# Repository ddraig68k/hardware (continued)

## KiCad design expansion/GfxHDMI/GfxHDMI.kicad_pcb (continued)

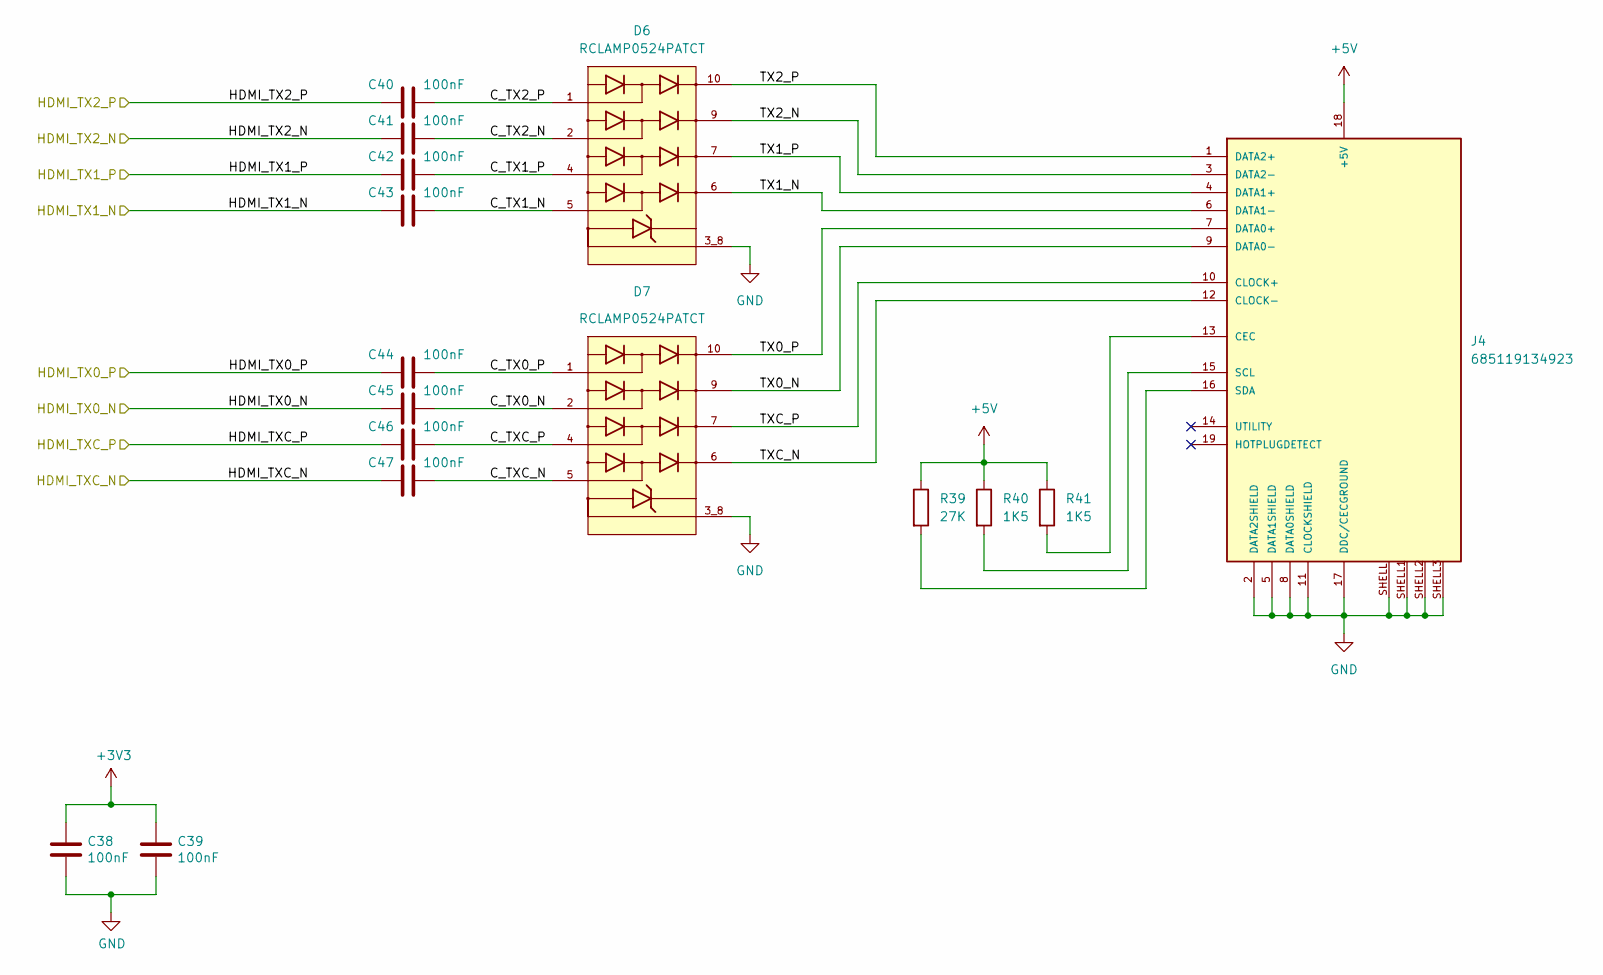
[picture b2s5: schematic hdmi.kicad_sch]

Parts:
C38, C39: 100nF; C_0805_2012Metric
C40, C41, C42, C43, C44, C45, C46, C47: 100nF; C_0603_1608Metric
D6, D7: RCLAMP0524PATCT; DIO_RCLAMP0524PATCT
J4: 685119134923
R39: 27K; R_0805_2012Metric
R40, R41: 1K5; R_0805_2012Metric

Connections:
+3V3: C38.1, C39.1; also elsewhere on the board
+5V: J4.18 (+5V), R39.1, R40.1, R41.1; also elsewhere on the board
/HDMI/C_TX0_N: C45.2, D7.2
/HDMI/C_TX0_P: C44.2, D7.1
/HDMI/C_TX1_N: C43.2, D6.5
/HDMI/C_TX1_P: C42.2, D6.4
/HDMI/C_TX2_N: C41.2, D6.2
/HDMI/C_TX2_P: C40.2, D6.1
/HDMI/C_TXC_N: C47.2, D7.5
/HDMI/C_TXC_P: C46.2, D7.4
/HDMI/HDMI_TX0_N: C45.1; also elsewhere on the board
/HDMI/HDMI_TX0_P: C44.1; also elsewhere on the board
/HDMI/HDMI_TX1_N: C43.1; also elsewhere on the board
/HDMI/HDMI_TX1_P: C42.1; also elsewhere on the board
/HDMI/HDMI_TX2_N: C41.1; also elsewhere on the board
/HDMI/HDMI_TX2_P: C40.1; also elsewhere on the board
/HDMI/HDMI_TXC_N: C47.1; also elsewhere on the board
/HDMI/HDMI_TXC_P: C46.1; also elsewhere on the board
/HDMI/TX0_N: D7.9, J4.9 (DATA0-)
/HDMI/TX0_P: D7.10, J4.7 (DATA0+)
/HDMI/TX1_N: D6.6, J4.6 (DATA1-)
/HDMI/TX1_P: D6.7, J4.4 (DATA1+)
/HDMI/TX2_N: D6.9, J4.3 (DATA2-)
/HDMI/TX2_P: D6.10, J4.1 (DATA2+)
/HDMI/TXC_N: D7.6, J4.12 (CLOCK-)
/HDMI/TXC_P: D7.7, J4.10 (CLOCK+)
GND: C38.2, C39.2, D6.3_8, D7.3_8, J4.2 (DATA2SHIELD), J4.5 (DATA1SHIELD), J4.8 (DATA0SHIELD), J4.11 (CLOCKSHIELD), J4.17 (DDC/CECGROUND), J4.SHELL, J4.SHELL1, J4.SHELL2, J4.SHELL3; also elsewhere on the board
unnamed: J4.13 (CEC), R41.2
unnamed: J4.15 (SCL), R40.2
unnamed: J4.16 (SDA), R39.2

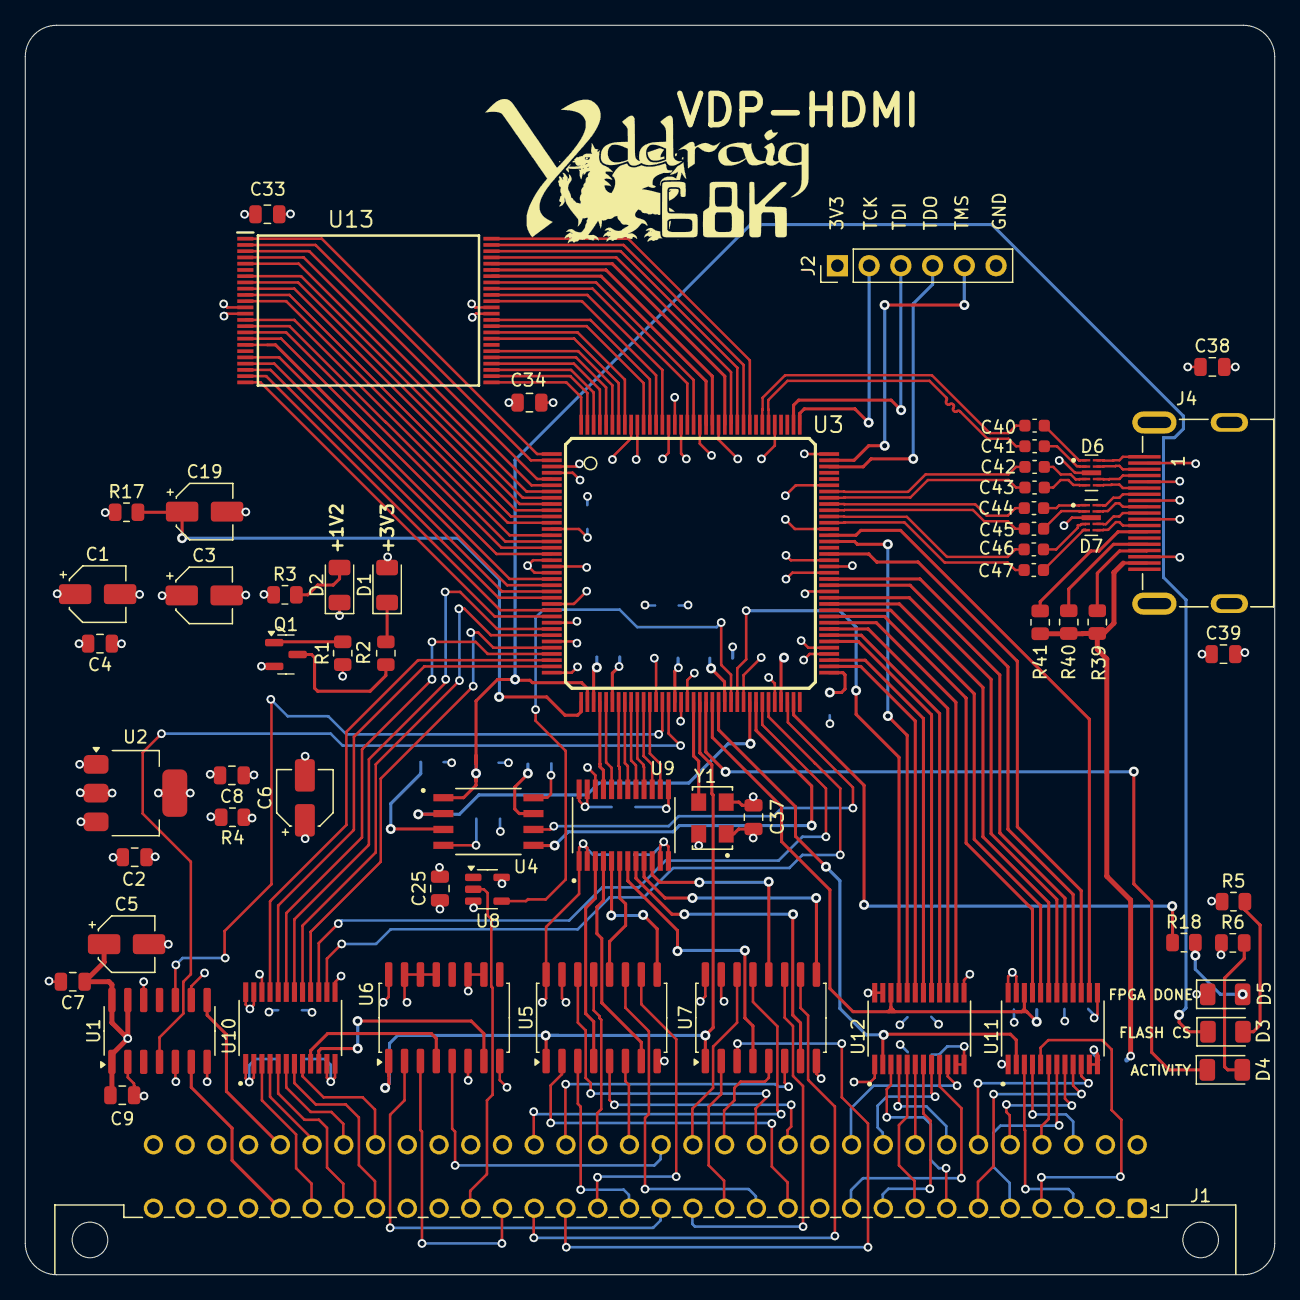
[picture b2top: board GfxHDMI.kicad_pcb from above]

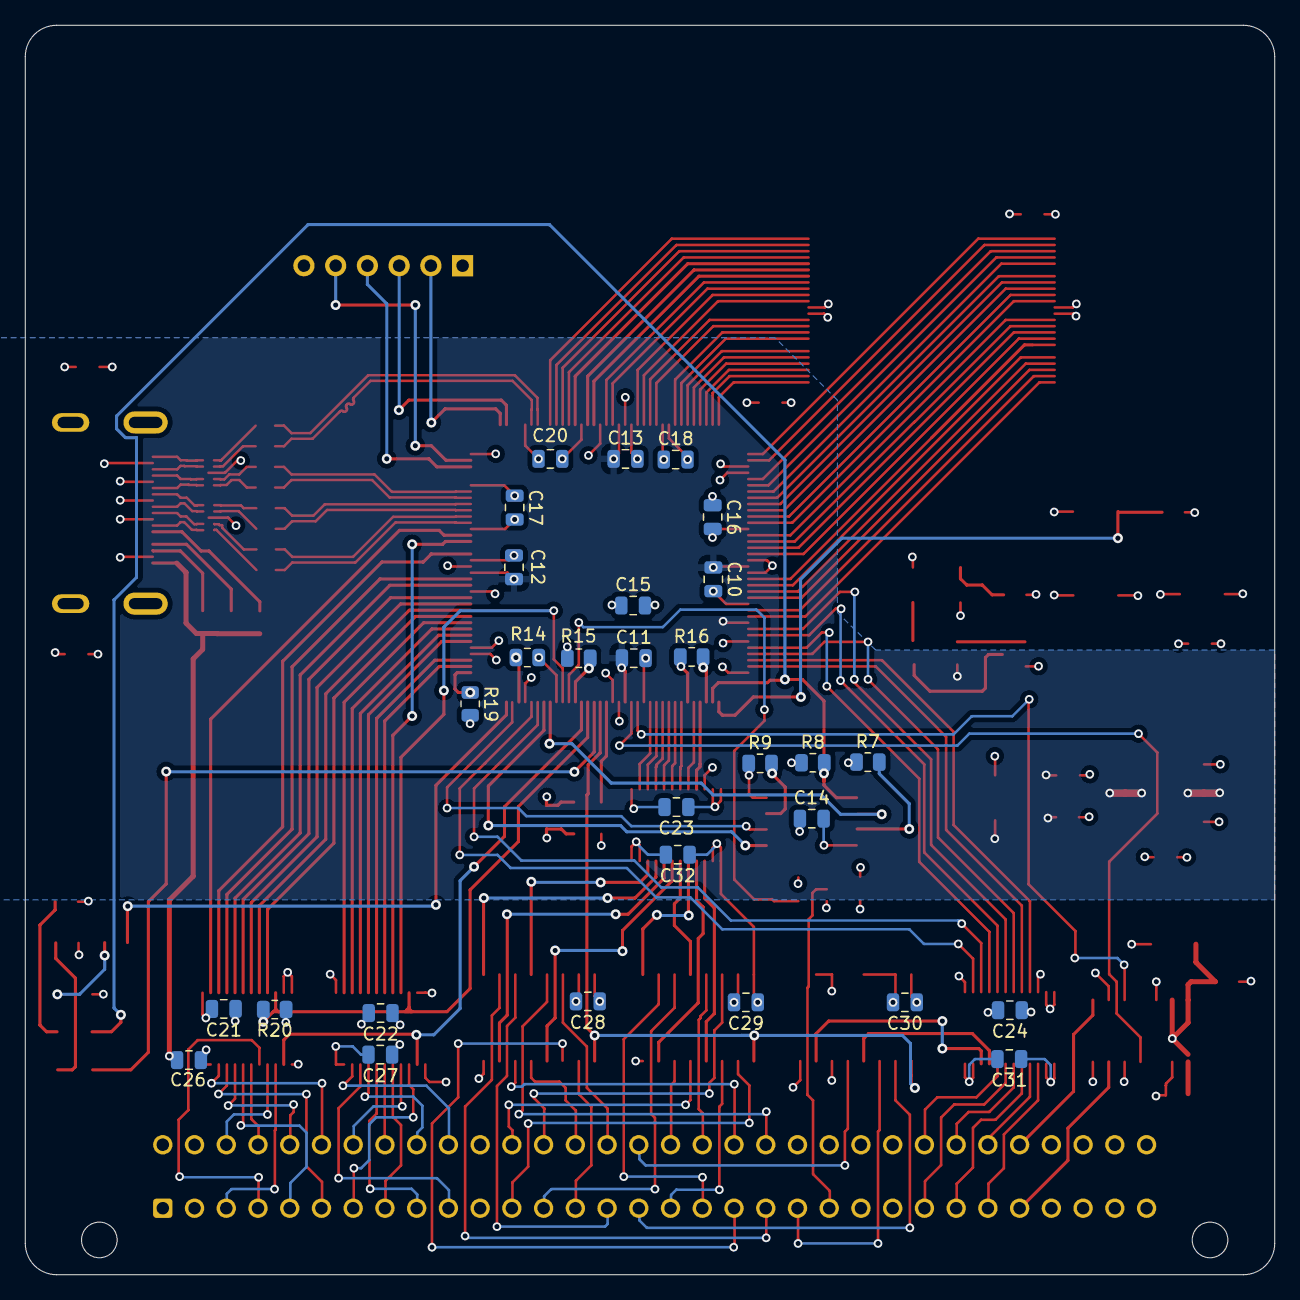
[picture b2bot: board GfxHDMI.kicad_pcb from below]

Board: 4 copper layers, 100.0 x 100.0 mm, 90 parts (29 on the bottom side), 189 nets.

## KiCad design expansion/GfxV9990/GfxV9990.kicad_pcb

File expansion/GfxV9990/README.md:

# V9990 Video card

The V9990 was intended as a successor to the V9958 (or supposedly a stripped down version of the never finished Yamaha V9978), but while the other chips in the range had backwards compatibility with the previous generation, the V9990 has some similar functionality but lacks the backwards compatibility.

Still, the V9990 has impressive specifications for the time, some of the features include:

Game Specifications:

For this type, there are two pattern display modes.
* P1 (Display resolution 256 x 212 2 screens)
* P2 (Display resolution 512 x 212)

*Various highly advanced functions are available such as powerful sprite function and omnidirectional scroll function.*

AV Specifications:

For this type, there are four kinds of bitmap display modes which can be displayed on the NTSC or PAL frequency monitor as follows.
* B1 (Display resolution 256 x 212)
* B2 (Display resolution 384 x 240)
* B3 (Display resolution 512 x 212)
* B4 (Display resolution 768 x 240)

*Capable of doubling the resolution in the vertical direction by using interlace.*
*Display is possible up to 32,768 colors/dot.*
*Built-in color palette (64 colors selected out of 32,768 colors).*
*Omnidirectional smooth scrolling is possible.*

Like the [V9958](/expansion/GfxV9958) card, the V9990 has Composite, S-Video and RGB output. The board has 518K of RAM installed and again uses CXA2075M encoder to provide the video output signals. 

**V9990 Text mode**

**Rygar scrolling test:** https://www.youtube.com/watch?v=J7Ad2eaiAFY

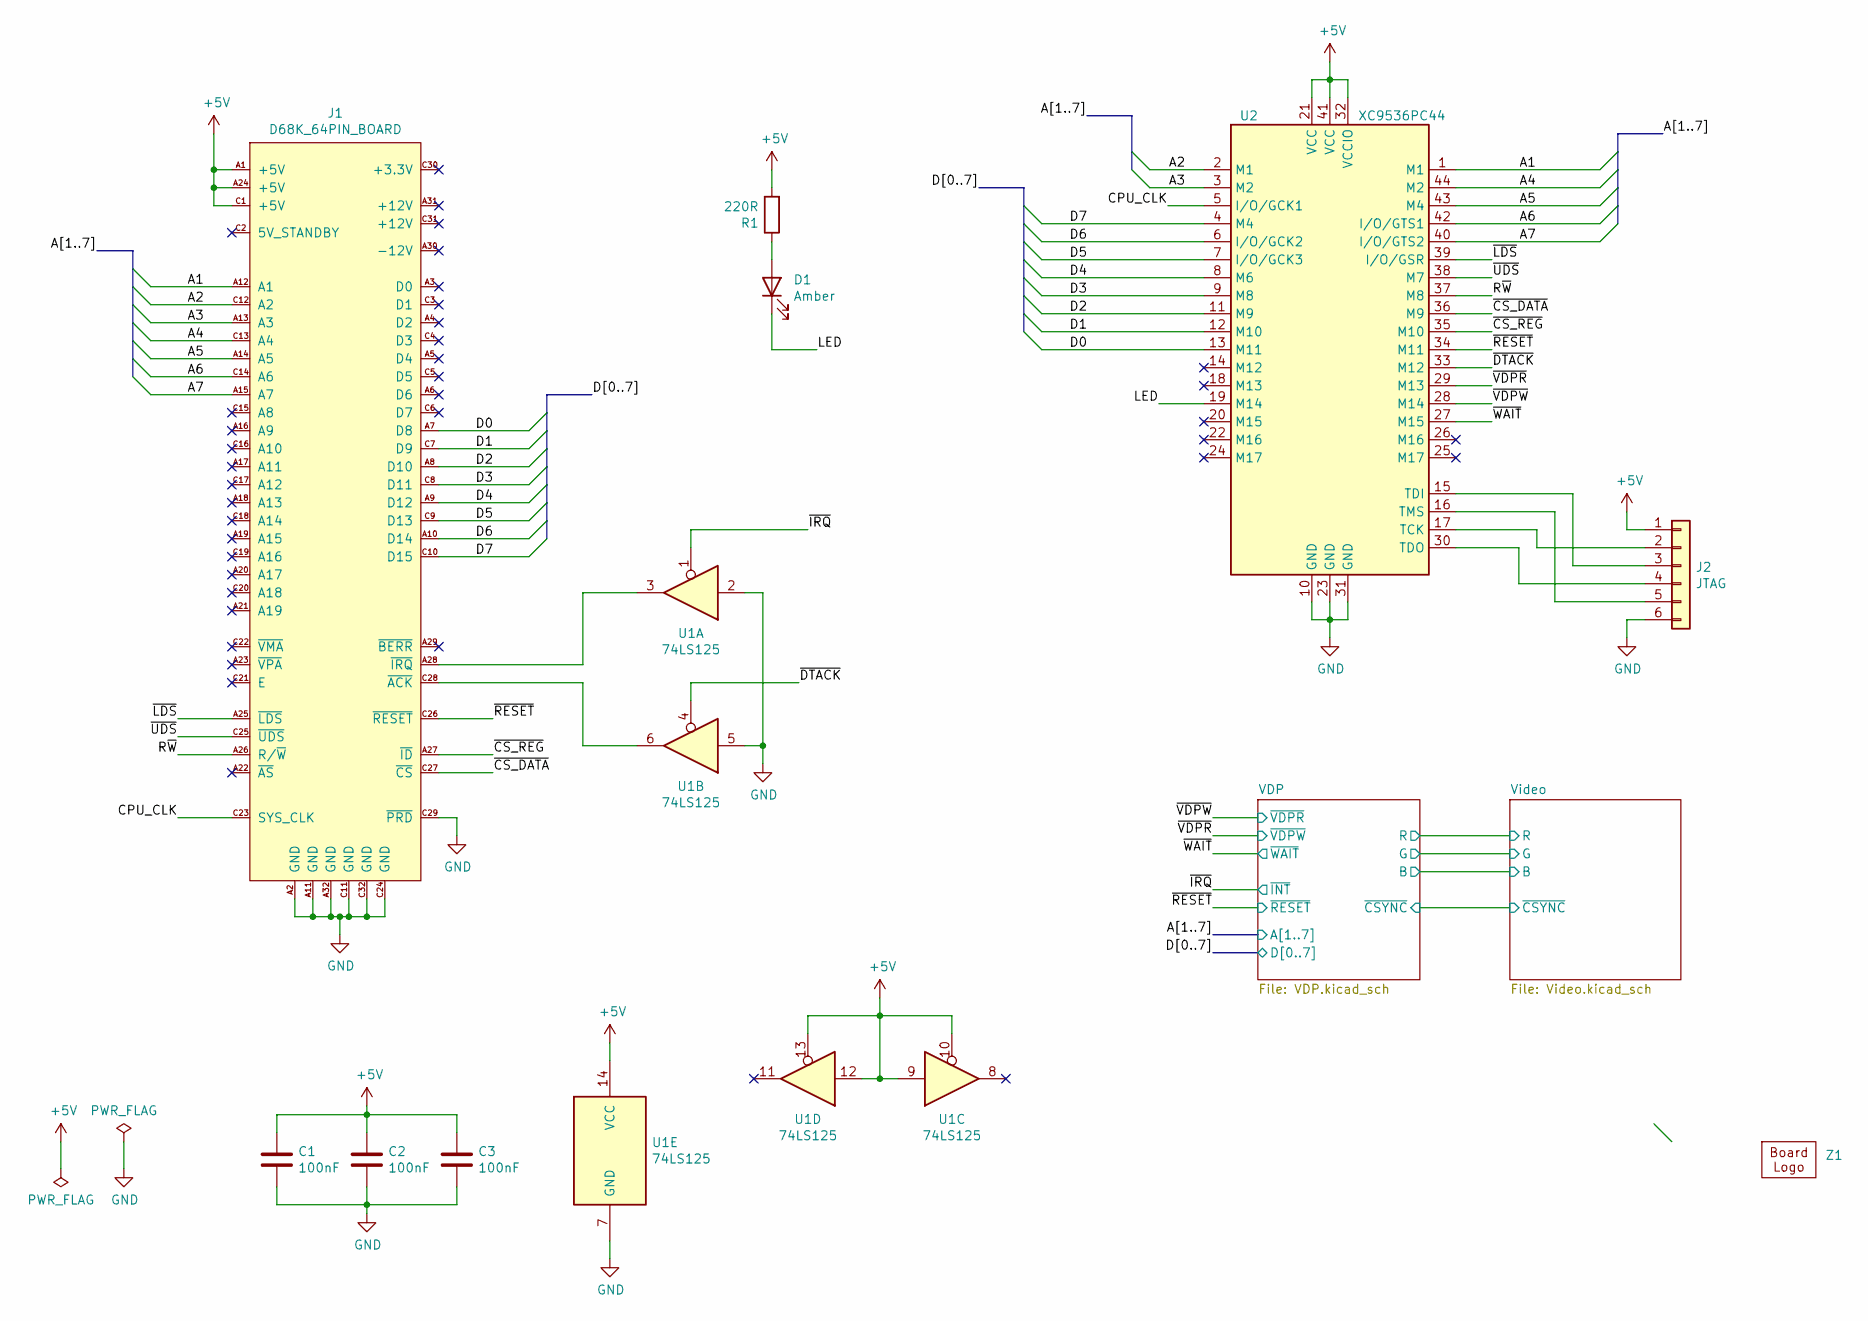
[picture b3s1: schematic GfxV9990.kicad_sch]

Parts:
C1, C2, C3: 100nF; C_0805_2012Metric
D1: Amber; LED_1206_3216Metric
J1: D68K_64PIN_BOARD; DIN41612_C_2x32_Male_Horizontal_THT
J2: JTAG; PinHeader_1x06_P2.54mm_Vertical
R1: 220R; LED_0805_2012Metric
U1: 74LS125; SO-14_3.9x8.65mm_P1.27mm
U2: XC9536PC44; PLCC-44_THT-Socket
Z1: Ddraig68k-26mm

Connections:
+5V: C1.1, C2.1, C3.1, J1.A1 (+5V), J1.A24 (+5V), J1.C1 (+5V), J2.1, R1.2, U1.9, U1.10, U1.12, U1.13, U1.14 (VCC), U2.21 (VCC), U2.32 (VCCIO), U2.41 (VCC); also elsewhere on the board
/A1: J1.A12 (A1), U2.1 (M1); also elsewhere on the board
/A2: J1.C12 (A2), U2.2 (M1); also elsewhere on the board
/A3: J1.A13 (A3), U2.3 (M2); also elsewhere on the board
/A4: J1.C13 (A4), U2.44 (M2); also elsewhere on the board
/A5: J1.A14 (A5), U2.43 (M4)
/A6: J1.C14 (A6), U2.42 (I/O/GTS1)
/A7: J1.A15 (A7), U2.40 (I/O/GTS2)
/CPU_CLK: J1.C23 (SYS_CLK), U2.5 (I/O/GCK1)
/D0: J1.A7 (D8), U2.13 (M11); also elsewhere on the board
/D1: J1.C7 (D9), U2.12 (M10); also elsewhere on the board
/D2: J1.A8 (D10), U2.11 (M9); also elsewhere on the board
/D3: J1.C8 (D11), U2.9 (M8); also elsewhere on the board
/D4: J1.A9 (D12), U2.8 (M6); also elsewhere on the board
/D5: J1.C9 (D13), U2.7 (I/O/GCK3); also elsewhere on the board
/D6: J1.A10 (D14), U2.6 (I/O/GCK2); also elsewhere on the board
/D7: J1.C10 (D15), U2.4 (M4); also elsewhere on the board
/LED: D1.1 (K), U2.19 (M14)
/R~W: J1.A26 (R/~W), U2.37 (M8)
/~CS_DATA: J1.C27 (~CS), U2.36 (M9)
/~CS_REG: J1.A27 (~ID), U2.35 (M10)
/~DTACK: U1.4, U2.33 (M12)
/~IRQ: U1.1; also elsewhere on the board
/~LDS: J1.A25 (~LDS), U2.39 (I/O/GSR)
/~RESET: J1.C26 (~RESET), U2.34 (M11); also elsewhere on the board
/~UDS: J1.C25 (~UDS), U2.38 (M7)
/~VDPR: U2.29 (M13); also elsewhere on the board
/~VDPW: U2.28 (M14); also elsewhere on the board
/~WAIT: U2.27 (M15); also elsewhere on the board
GND: C1.2, C2.2, C3.2, J1.A2 (GND), J1.A11 (GND), J1.A32 (GND), J1.C11 (GND), J1.C24 (GND), J1.C29 (~PRD), J1.C32 (GND), J2.6, U1.2, U1.5, U1.7 (GND), U2.10 (GND), U2.23 (GND), U2.31 (GND); also elsewhere on the board
unnamed: D1.2 (A), R1.1
unnamed: J1.A28 (~IRQ), U1.3
unnamed: J1.C28 (~ACK), U1.6
unnamed: J2.2, U2.17 (TCK)
unnamed: J2.3, U2.15 (TDI)
unnamed: J2.4, U2.30 (TDO)
unnamed: J2.5, U2.16 (TMS)

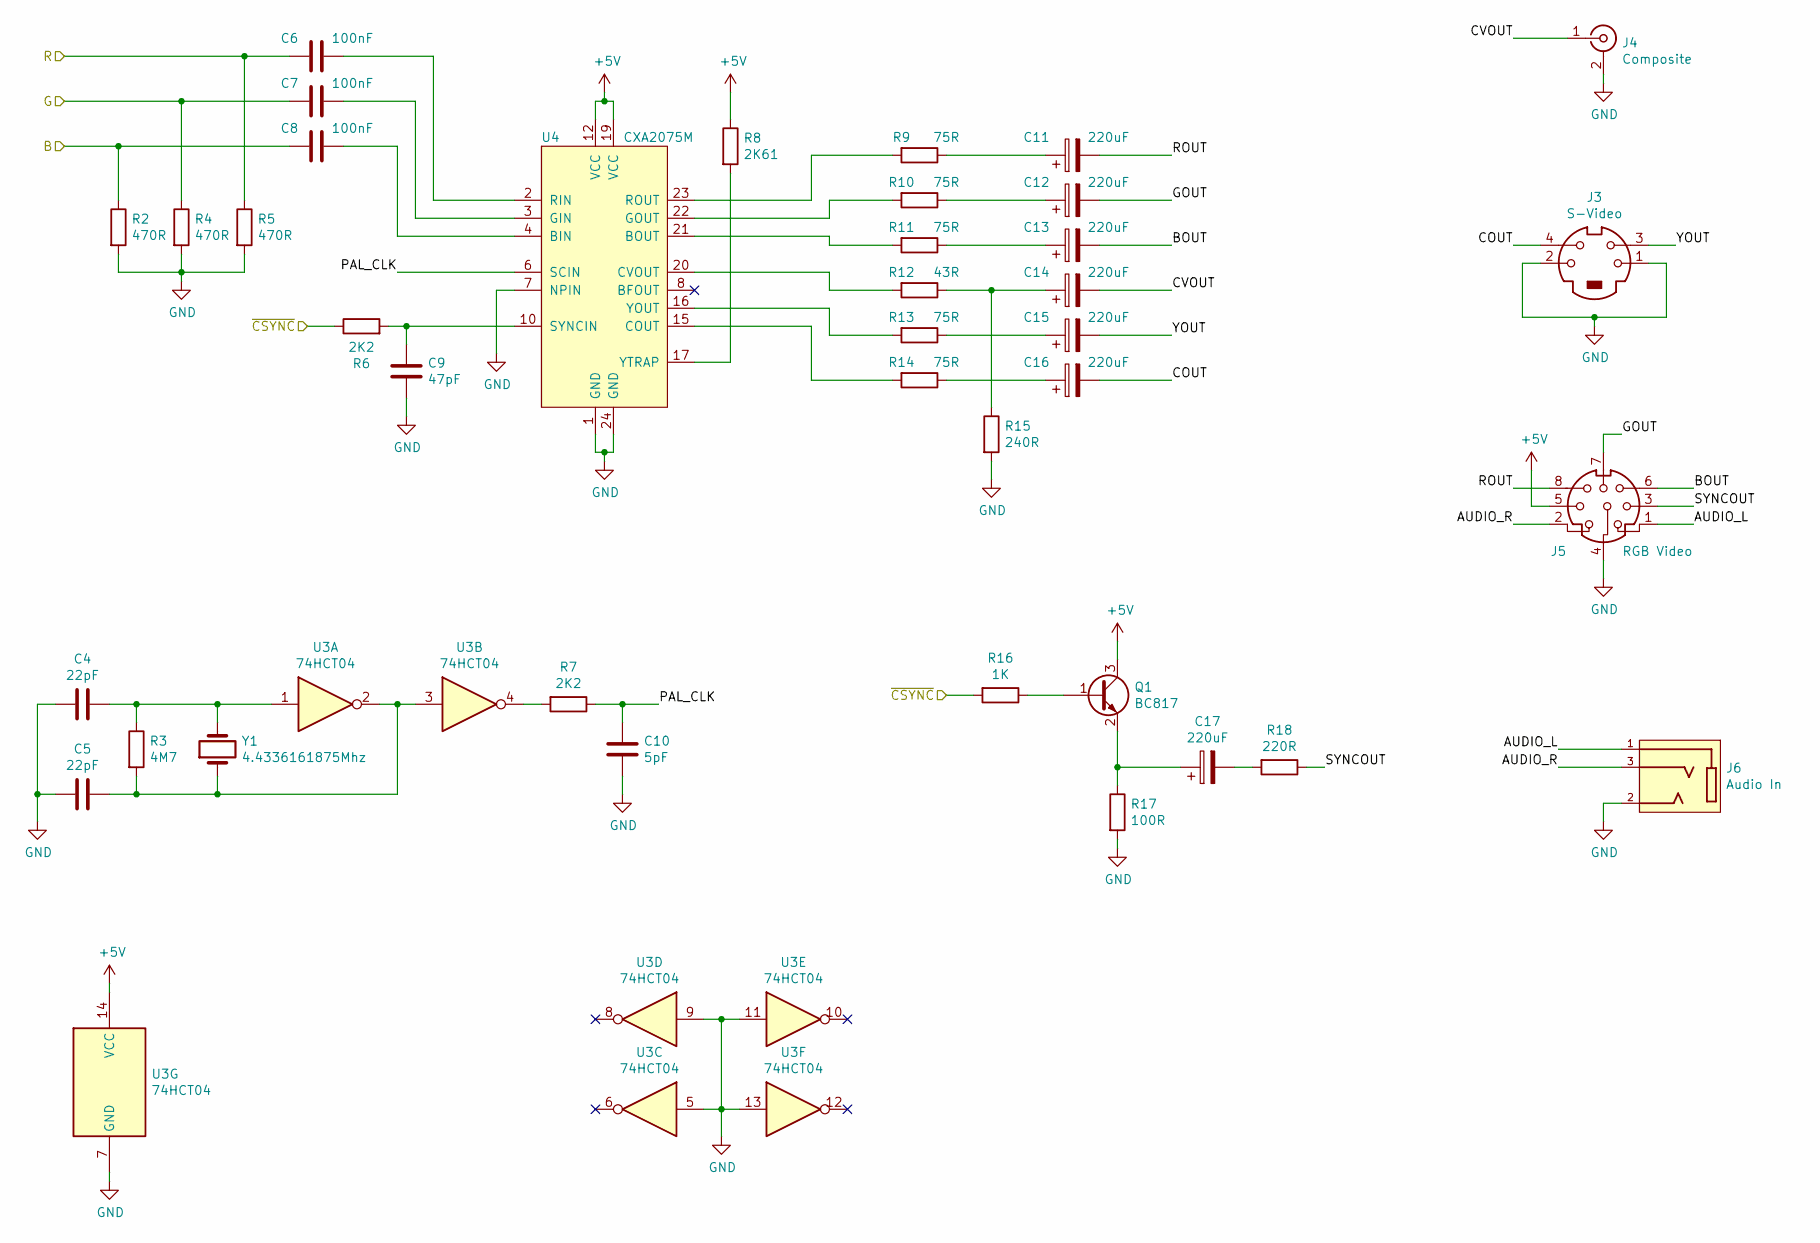
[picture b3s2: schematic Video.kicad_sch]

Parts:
C4, C5: 22pF; C_0805_2012Metric
C6, C7, C8: 100nF; C_0805_2012Metric
C9: 47pF; C_0805_2012Metric
C10: 5pF; C_0805_2012Metric
C11, C12, C13, C14, C15, C16, C17: 220uF; CP_Radial_D5.0mm_P2.50mm
J3: S-Video; MINI-DIN-4-TE_5749181-1
J4: Composite; KLPX0848A2RG
J5: RGB Video; MINI-DIN-8-TE_57492681
J6: Audio In; SWITCHCRAFT_35RAPC2BHN2; PARTREV L
Q1: BC817; SOT-23
R2, R4, R5: 470R; LED_0805_2012Metric
R3: 4M7; LED_0805_2012Metric
R6, R7: 2K2; LED_0805_2012Metric
R8: 2K61; LED_0805_2012Metric
R9, R10, R11, R13, R14: 75R; LED_0805_2012Metric
R12: 43R; LED_0805_2012Metric
R15: 240R; LED_0805_2012Metric
R16: 1K; LED_0805_2012Metric
R17: 100R; LED_0805_2012Metric
R18: 220R; LED_0805_2012Metric
U3: 74HCT04; SO-14_3.9x8.65mm_P1.27mm
U4: CXA2075M; SOP-24_7.5x15.4mm_P1.27mm
Y1: 4.4336161875Mhz; Crystal_HC50_Vertical

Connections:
+5V: J5.5, Q1.3 (C), R8.1, U3.14 (VCC), U4.12 (VCC), U4.19 (VCC); also elsewhere on the board
/VDP/B: C8.2, R2.1; also elsewhere on the board
/VDP/G: C7.2, R4.1; also elsewhere on the board
/VDP/R: C6.2, R5.1; also elsewhere on the board
/VDP/~CSYNC: R6.1, R16.2; also elsewhere on the board
/Video/AUDIO_L: J5.1, J6.1
/Video/AUDIO_R: J5.2, J6.3
/Video/BOUT: C13.2, J5.6
/Video/COUT: C16.2, J3.4
/Video/CVOUT: C14.2, J4.1 (In)
/Video/GOUT: C12.2, J5.7
/Video/PAL_CLK: C10.1, R7.1, U4.6 (SCIN)
/Video/ROUT: C11.2, J5.8
/Video/SYNCOUT: J5.3, R18.1
/Video/YOUT: C15.2, J3.3
GND: C4.2, C5.2, C9.2, C10.2, J3.1, J3.2, J4.2 (Ext), J5.4, J6.2, R2.2, R4.2, R5.2, R15.2, R17.2, U3.5, U3.7 (GND), U3.9, U3.11, U3.13, U4.1 (GND), U4.7 (NPIN), U4.24 (GND); also elsewhere on the board
unnamed: C4.1, R3.1, U3.1, Y1.2
unnamed: C5.1, R3.2, U3.2, U3.3, Y1.1
unnamed: C6.1, U4.2 (RIN)
unnamed: C7.1, U4.3 (GIN)
unnamed: C8.1, U4.4 (BIN)
unnamed: C9.1, R6.2, U4.10 (SYNCIN)
unnamed: C11.1, R9.1
unnamed: C12.1, R10.1
unnamed: C13.1, R11.1
unnamed: C14.1, R12.1, R15.1
unnamed: C15.1, R13.1
unnamed: C16.1, R14.1
unnamed: C17.1, Q1.2 (E), R17.1
unnamed: C17.2, R18.2
unnamed: Q1.1 (B), R16.1
unnamed: R7.2, U3.4
unnamed: R8.2, U4.17 (YTRAP)
unnamed: R9.2, U4.23 (ROUT)
unnamed: R10.2, U4.22 (GOUT)
unnamed: R11.2, U4.21 (BOUT)
unnamed: R12.2, U4.20 (CVOUT)
unnamed: R13.2, U4.16 (YOUT)
unnamed: R14.2, U4.15 (COUT)

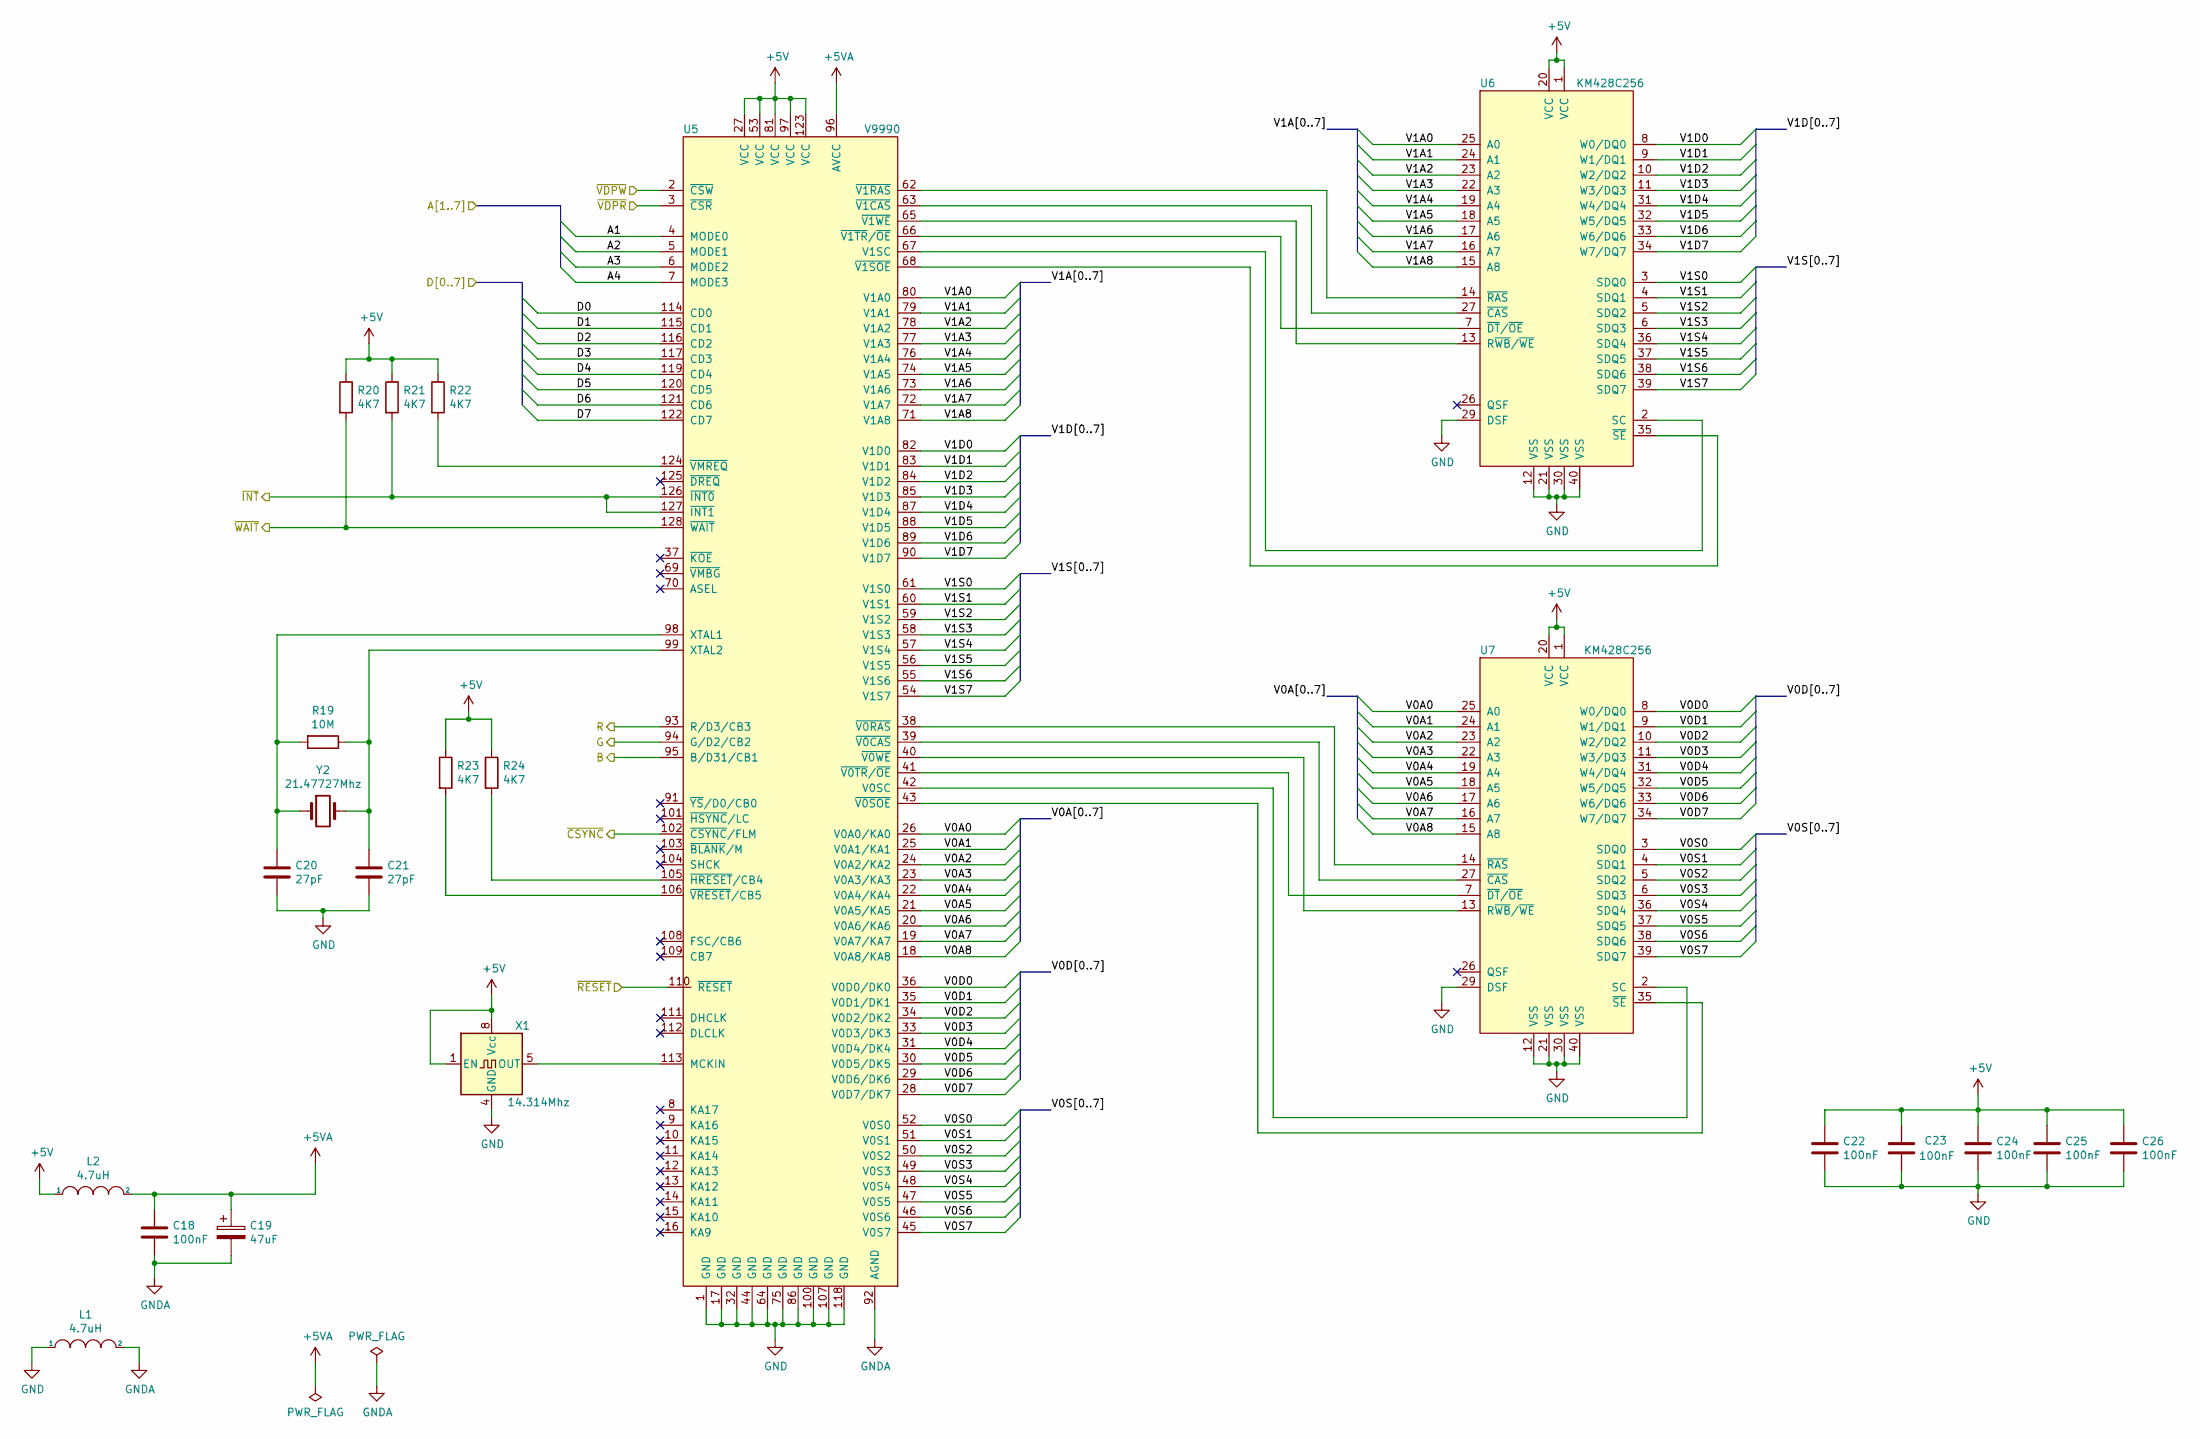
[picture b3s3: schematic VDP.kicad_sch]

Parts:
C18, C22, C23, C24, C25, C26: 100nF; C_0805_2012Metric
C19: 47uF; CP_Radial_D5.0mm_P2.50mm
C20, C21: 27pF; C_0805_2012Metric
L1, L2: 4.7uH; L_1206_3216Metric
R19: 10M; LED_0805_2012Metric
R20, R21, R22, R23, R24: 4K7; LED_0805_2012Metric
U5: V9990; QFP-128_28x28_Pitch0.8mm
U6, U7: KM428C256; SOIC-40
X1: 14.314Mhz; Oscillator_DIP-8
Y2: 21.47727Mhz; Crystal_HC50_Vertical

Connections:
+5V: C22.1, C23.2, C24.1, C25.1, C26.1, L2.1, R20.1, R21.1, R22.1, R23.1, R24.1, U5.27 (VCC), U5.53 (VCC), U5.81 (VCC), U5.97 (VCC), U5.123 (VCC), U6.1 (VCC), U6.20 (VCC), U7.1 (VCC), U7.20 (VCC), X1.1 (EN), X1.8 (Vcc); also elsewhere on the board
+5VA: C18.1, C19.1, L2.2, U5.96 (AVCC)
/A1: U5.4 (MODE0); also elsewhere on the board
/A2: U5.5 (MODE1); also elsewhere on the board
/A3: U5.6 (MODE2); also elsewhere on the board
/A4: U5.7 (MODE3); also elsewhere on the board
/D0: U5.114 (CD0); also elsewhere on the board
/D1: U5.115 (CD1); also elsewhere on the board
/D2: U5.116 (CD2); also elsewhere on the board
/D3: U5.117 (CD3); also elsewhere on the board
/D4: U5.119 (CD4); also elsewhere on the board
/D5: U5.120 (CD5); also elsewhere on the board
/D6: U5.121 (CD6); also elsewhere on the board
/D7: U5.122 (CD7); also elsewhere on the board
/VDP/B: U5.95 (B/D31/CB1); also elsewhere on the board
/VDP/G: U5.94 (G/D2/CB2); also elsewhere on the board
/VDP/R: U5.93 (R/D3/CB3); also elsewhere on the board
/VDP/V0A0: U5.26 (V0A0/KA0), U7.25 (A0)
/VDP/V0A1: U5.25 (V0A1/KA1), U7.24 (A1)
/VDP/V0A2: U5.24 (V0A2/KA2), U7.23 (A2)
/VDP/V0A3: U5.23 (V0A3/KA3), U7.22 (A3)
/VDP/V0A4: U5.22 (V0A4/KA4), U7.19 (A4)
/VDP/V0A5: U5.21 (V0A5/KA5), U7.18 (A5)
/VDP/V0A6: U5.20 (V0A6/KA6), U7.17 (A6)
/VDP/V0A7: U5.19 (V0A7/KA7), U7.16 (A7)
/VDP/V0A8: U5.18 (V0A8/KA8), U7.15 (A8)
/VDP/V0D0: U5.36 (V0D0/DK0), U7.8 (W0/DQ0)
/VDP/V0D1: U5.35 (V0D1/DK1), U7.9 (W1/DQ1)
/VDP/V0D2: U5.34 (V0D2/DK2), U7.10 (W2/DQ2)
/VDP/V0D3: U5.33 (V0D3/DK3), U7.11 (W3/DQ3)
/VDP/V0D4: U5.31 (V0D4/DK4), U7.31 (W4/DQ4)
/VDP/V0D5: U5.30 (V0D5/DK5), U7.32 (W5/DQ5)
/VDP/V0D6: U5.29 (V0D6/DK6), U7.33 (W6/DQ6)
/VDP/V0D7: U5.28 (V0D7/DK7), U7.34 (W7/DQ7)
/VDP/V0S0: U5.52 (V0S0), U7.3 (SDQ0)
/VDP/V0S1: U5.51 (V0S1), U7.4 (SDQ1)
/VDP/V0S2: U5.50 (V0S2), U7.5 (SDQ2)
/VDP/V0S3: U5.49 (V0S3), U7.6 (SDQ3)
/VDP/V0S4: U5.48 (V0S4), U7.36 (SDQ4)
/VDP/V0S5: U5.47 (V0S5), U7.37 (SDQ5)
/VDP/V0S6: U5.46 (V0S6), U7.38 (SDQ6)
/VDP/V0S7: U5.45 (V0S7), U7.39 (SDQ7)
/VDP/V1A0: U5.80 (V1A0), U6.25 (A0)
/VDP/V1A1: U5.79 (V1A1), U6.24 (A1)
/VDP/V1A2: U5.78 (V1A2), U6.23 (A2)
/VDP/V1A3: U5.77 (V1A3), U6.22 (A3)
/VDP/V1A4: U5.76 (V1A4), U6.19 (A4)
/VDP/V1A5: U5.74 (V1A5), U6.18 (A5)
/VDP/V1A6: U5.73 (V1A6), U6.17 (A6)
/VDP/V1A7: U5.72 (V1A7), U6.16 (A7)
/VDP/V1A8: U5.71 (V1A8), U6.15 (A8)
/VDP/V1D0: U5.82 (V1D0), U6.8 (W0/DQ0)
/VDP/V1D1: U5.83 (V1D1), U6.9 (W1/DQ1)
/VDP/V1D2: U5.84 (V1D2), U6.10 (W2/DQ2)
/VDP/V1D3: U5.85 (V1D3), U6.11 (W3/DQ3)
/VDP/V1D4: U5.87 (V1D4), U6.31 (W4/DQ4)
/VDP/V1D5: U5.88 (V1D5), U6.32 (W5/DQ5)
/VDP/V1D6: U5.89 (V1D6), U6.33 (W6/DQ6)
/VDP/V1D7: U5.90 (V1D7), U6.34 (W7/DQ7)
/VDP/V1S0: U5.61 (V1S0), U6.3 (SDQ0)
/VDP/V1S1: U5.60 (V1S1), U6.4 (SDQ1)
/VDP/V1S2: U5.59 (V1S2), U6.5 (SDQ2)
/VDP/V1S3: U5.58 (V1S3), U6.6 (SDQ3)
/VDP/V1S4: U5.57 (V1S4), U6.36 (SDQ4)
/VDP/V1S5: U5.56 (V1S5), U6.37 (SDQ5)
/VDP/V1S6: U5.55 (V1S6), U6.38 (SDQ6)
/VDP/V1S7: U5.54 (V1S7), U6.39 (SDQ7)
/VDP/~CSYNC: U5.102 (~CSYNC/FLM); also elsewhere on the board
/~IRQ: R21.2, U5.126 (~INT0), U5.127 (~INT1); also elsewhere on the board
/~RESET: U5.110 (~RESET); also elsewhere on the board
/~VDPR: U5.2 (~CSW); also elsewhere on the board
/~VDPW: U5.3 (~CSR); also elsewhere on the board
/~WAIT: R20.2, U5.128 (~WAIT); also elsewhere on the board
GND: C20.2, C21.2, C22.2, C23.1, C24.2, C25.2, C26.2, L1.1, U5.1 (GND), U5.17 (GND), U5.32 (GND), U5.44 (GND), U5.64 (GND), U5.75 (GND), U5.86 (GND), U5.100 (GND), U5.107 (GND), U5.118 (GND), U6.12 (VSS), U6.21 (VSS), U6.29 (DSF), U6.30 (VSS), U6.40 (VSS), U7.12 (VSS), U7.21 (VSS), U7.29 (DSF), U7.30 (VSS), U7.40 (VSS), X1.4 (GND); also elsewhere on the board
GNDA: C18.2, C19.2, L1.2, U5.92 (AGND)
unnamed: C20.1, R19.2, U5.98 (XTAL1), Y2.1
unnamed: C21.1, R19.1, U5.99 (XTAL2), Y2.2
unnamed: R22.2, U5.124 (~VMREQ)
unnamed: R23.2, U5.106 (~VRESET/CB5)
unnamed: R24.2, U5.105 (~HRESET/CB4)
unnamed: U5.38 (~V0RAS), U7.14 (~RAS)
unnamed: U5.39 (~V0CAS), U7.27 (~CAS)
unnamed: U5.40 (~V0WE), U7.13 (R~WB/~WE)
unnamed: U5.41 (~V0TR/~OE), U7.7 (~DT/~OE)
unnamed: U5.42 (V0SC), U7.2 (SC)
unnamed: U5.43 (~V0SOE), U7.35 (~SE)
unnamed: U5.62 (~V1RAS), U6.14 (~RAS)
unnamed: U5.63 (~V1CAS), U6.27 (~CAS)
unnamed: U5.65 (~V1WE), U6.13 (R~WB/~WE)
unnamed: U5.66 (~V1TR/~OE), U6.7 (~DT/~OE)
unnamed: U5.67 (V1SC), U6.2 (SC)
unnamed: U5.68 (~V1SOE), U6.35 (~SE)
unnamed: U5.113 (MCKIN), X1.5 (OUT)

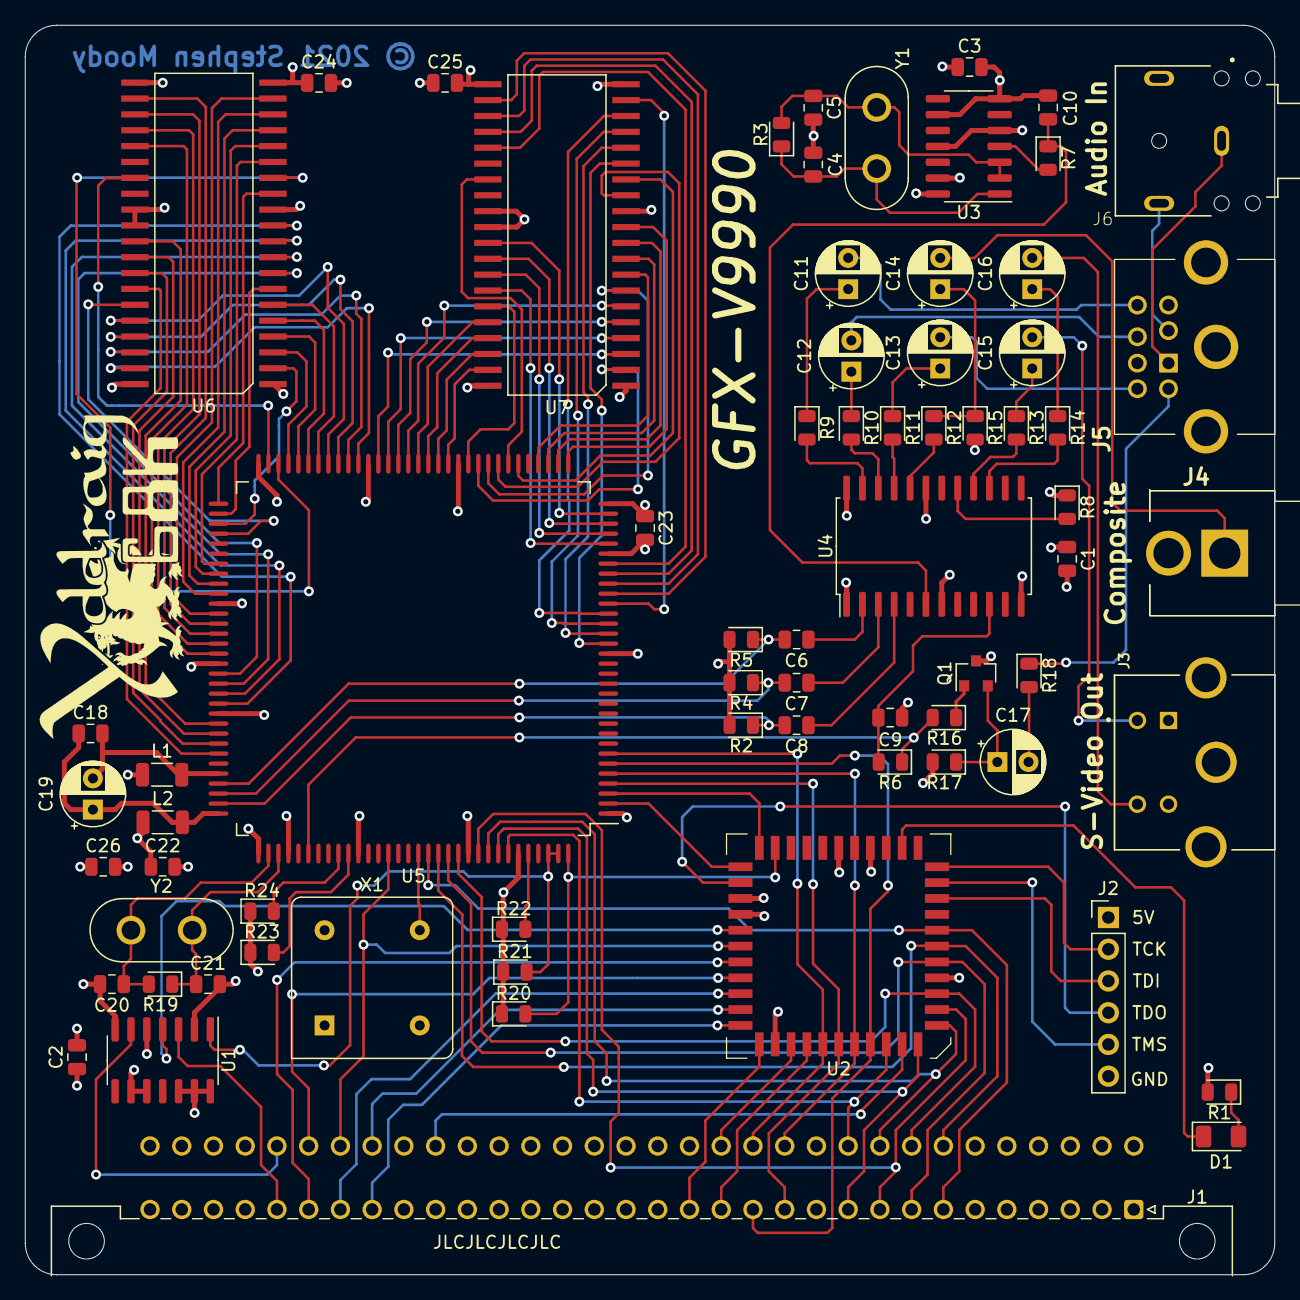
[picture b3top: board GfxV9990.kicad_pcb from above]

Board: 4 copper layers, 100.0 x 100.0 mm, 70 parts (0 on the bottom side), 144 nets.
